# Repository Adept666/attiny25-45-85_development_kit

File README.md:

# attiny25-45-85_development_kit

ATtiny25/45/85 Development Kit

## Author

Igor Ivanov

## License

This project is licensed under GNU General Public License v3.0 or later

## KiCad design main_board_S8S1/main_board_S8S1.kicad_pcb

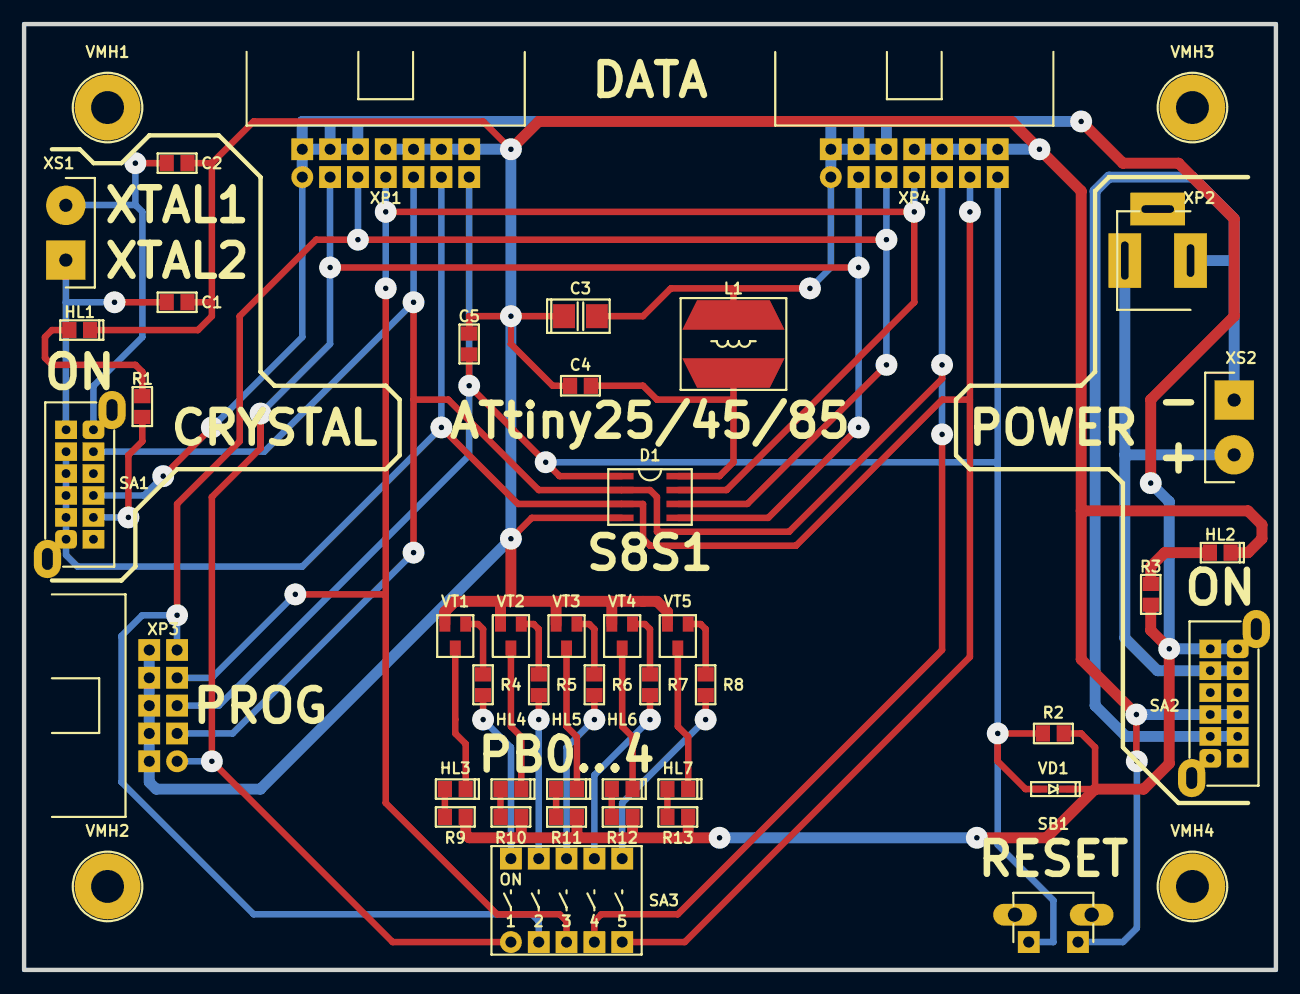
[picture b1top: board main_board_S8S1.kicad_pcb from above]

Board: 2 copper layers, 114.3 x 86.4 mm, 47 parts (0 on the bottom side), 36 nets.

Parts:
C1, C2, C4, C5: CAPACITOR_NON-POLARIZED; C-SMD-0805
C3: CAPACITOR_POLARIZED; CP-SMD-3528
D1: ATtiny25-20SSU; P-SO-08
HL1, HL2, HL3, HL4, HL5, HL6, HL7: DIODE_LIGHT-EMITTING_LEFT; LED-SMD-0805
L1: INDUCTOR_FMC; I-SDR0805
R1, R2, R3, R4, R5, R6, R7, R8, R9, R10, R11, R12, R13: RESISTOR_GENERAL; R-SMD-0805
SA1, SA2: SWITCH_GENERAL_04P_02T; SW-SK-42D01-G
SA3: SWITCH_GENERAL_01P_01T_NO_05U; SW-NDI(R)-05
SB1: SWITCH_BUTTON_NON-LOCK_01P_01T_NO; SW-07125
VD1: DIODE_GENERAL; P-SOD-323
VMH1, VMH2, VMH3, VMH4: VIRTUAL_MOUNTING-HOLE; VMH-STA-DA5
VT1, VT2, VT3, VT4, VT5: BJT_NPN_GENERAL; P-SOT-23
XP1, XP4: CONNECTOR_M_014_20_DATA; CON-IDC-14MR
XP2: CONNECTOR_M_BARREL_SW; CON-PJ-002B
XP3: CONNECTOR_M_010_20_PROG; CON-IDC-10MR
XS1: CONNECTOR_F_002_20_CRYSTAL; CON-DG301R-5.0-02P
XS2: CONNECTOR_F_002_20_POWER; CON-DG301R-5.0-02P

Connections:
/PB0: D1.5, SA3.1COM, XP1.3, XP3.1, XP4.3
/PB1: D1.6, SA3.2COM, XP1.5, XP3.9, XP4.5
/PB2: D1.7, SA3.3COM, XP1.7, XP3.7, XP4.7
/PB3: D1.2, SA1.COM1, SA3.4COM, XP1.9, XP3.3, XP4.9
/PB4: D1.3, SA1.COM3, SA1.COM4, SA1.NC4, SA1.NO3, SA1.NO4, SA3.5COM, XP1.11, XP4.11
/PB5: C5.1, D1.1, R2.2, SB1.NO, VD1.A, XP1.13, XP3.5, XP4.13
/VCC: C4.1, D1.8, L1.2
COM: C1.2, C2.2, C3.-, C4.2, C5.2, D1.4, HL1.C, HL2.C, SA2.NO1, SA2.NO3, SB1.COM, VT1.E, VT2.E, VT3.E, VT4.E, VT5.E, XP1.8, XP1.10, XP1.12, XP1.14, XP3.2, XP3.4, XP3.6, XP3.8, XP3.10, XP4.8, XP4.10, XP4.12, XP4.14
unnamed: C1.1, SA1.NC3, XS1.2
unnamed: C2.1, SA1.NC1, XS1.1
unnamed: HL1.A, R1.2
unnamed: HL2.A, R3.2
unnamed: HL3.A, R9.1
unnamed: HL3.C, VT1.C
unnamed: HL4.A, R10.1
unnamed: HL4.C, VT2.C
unnamed: HL5.A, R11.1
unnamed: HL5.C, VT3.C
unnamed: HL6.A, R12.1
unnamed: HL6.C, VT4.C
unnamed: HL7.A, R13.1
unnamed: HL7.C, VT5.C
unnamed: R1.1, SA1.COM2
unnamed: R4.1, SA3.1NO
unnamed: R4.2, VT1.B
unnamed: R5.1, SA3.2NO
unnamed: R5.2, VT2.B
unnamed: R6.1, SA3.3NO
unnamed: R6.2, VT3.B
unnamed: R7.1, SA3.4NO
unnamed: R7.2, VT4.B
unnamed: R8.1, SA3.5NO
unnamed: R8.2, VT5.B
unnamed: SA2.COM1, SA2.COM3, XS2.2
unnamed: SA2.COM2, SA2.COM4, XS2.1
V: C3.+, L1.1, R2.1, R3.1, R9.2, R10.2, R11.2, R12.2, R13.2, SA1.NC2, SA2.NO2, SA2.NO4, VD1.C, XP1.1, XP1.2, XP1.4, XP1.6, XP4.1, XP4.2, XP4.4, XP4.6

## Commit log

2018-04-19 Add files via upload
    ATtiny debug board
2018-08-10 Rename ATtiny25 debug board. Main board-cache.lib to main_board_S8S1-cache.lib
2018-08-10 Rename main_board_S8S1-cache.lib to main_board_S8S1/main_board_S8S1-cache.lib
2018-08-10 Rename ATtiny25 debug board. Main board.kicad_pcb to main_board_S8S1/main_board_S8S1.kicad_pcb
2018-08-10 Rename ATtiny25 debug board. Main board.net to main_board_S8S1/main_board_S8S1.net
2018-08-10 Rename ATtiny25 debug board. Main board.pro to main_board_S8S1/main_board_S8S1.pro
2018-08-10 Rename ATtiny25 debug board. Main board.sch to main_board_S8S1/main_board_S8S1.sch
2018-08-10 Rename KCPL.lib to main_board_S8S1/KCPL.lib
2018-08-10 Толщина линий на слое Edge.Cuts увеличена до 0,4 мм
2018-08-10 Заменён футпринт контроллера
2018-08-10 Заменён футпринт контроллера, изменены номиналы R1 и R3
2018-08-10 Заменён символ контроллера
2018-08-13 Обновлены футпринты ключей
2018-08-13 Обновлён футпринт диода
2018-08-13 Все слои сделаны видимыми
2018-08-13 Чертежи подписаны
2018-08-17 Обновлены футпринты разъёмов и ключей
2018-08-17 Обновлены футпринты светодиодов
2018-10-29 Удалён файл нетлиста
2018-10-29 Обновлены футпринты светодиодов HL1, HL2
2018-10-29 Доработаны трассы, а также линии на слое F.SilkS (разделённые линии заменены цельными)
2018-10-29 Удалён файл библиотеки main_board_S8S1-cache.lib
2018-10-29 Файл библиотеки символов переименован в соответствии с названием проекта
2018-10-31 В связи с доработкой библиотеки обновлено большинство футпринтов
2019-02-17 Создан файл README.md
2019-02-17 Создано изображение схемы
2019-02-17 В README.md добавлено изображение схемы
2019-02-17 Изменена толщина печатной платы
2019-02-17 Буквенная нумерация составных частей компонентов заменена на цифровую
2019-02-17 Подписаны разъёмы, переключатели, светодиоды и ИМС. Скрыты имена футпринтов. Показана мощность резисторов. Свойства текстовых полей УГО приведены к единообразию
2019-02-17 Свойства текстовых полей составных частей УГО ключа SA3 приведены к единообразию
2019-02-17 Отключены неиспользуемые слои Adhes и Paste
2019-02-17 Отредактирована библиотека проекта. Обновлена схема и плата
2019-02-17 Применены собственные символы общей точки и питания. Завершено обновление схемы после дорабоки бибиотеки проекта
2019-02-18 В связи с доработкой библиотеки обновлены футпринты ключей
2019-02-18 Корректно выбраны значения свойства Placement Type футпринтов
2019-02-18 Обновлены футпринты (удалены примитивы на слое F.Paste)
2019-02-18 Спроектированы варианты основных плат для МК в корпусах 8P3 и 8S2. Повторно выбраны значения свойсва Placement Type футпринтов
2019-05-15 Обновлены УГО ИМС
2019-05-15 Незначительно отредактированы платы
2019-05-15 Основные надписи схем дополнены комментариями о лицензии
2019-05-15 Основные надписи плат дополнены комментариями о лицензии
2019-05-15 Обновлены изображения схем. Увеличена толщина линий
2019-07-12 Символы HOLE заменены на символы VIRTUAL_MOUNTING-HOLE. Скорректировано положение некоторых надписей слоя F.Fab
2019-07-12 Изображены соединения на шинах
2019-09-02 Обновлены футпринты разъёмов IDC
2019-09-02 Скорректированы библиотеки проектов
2019-09-04 Схемы и платы обновлены в связи с переименованием футпринта стойки VMH-STA-DA5
2019-09-04 Схемы скорректированы с учётом изменений в УГО переключателей
2019-09-04 Платы скорректированы с учётом изменений в ФП переключателей
2019-09-06 Незначительно оптимизирована трассировка
2019-09-13 Платы обновлены в связи с изменением футпринта VMH-STA-DA5
2019-11-04 Платы обновлены в связи с изменением футпринта CON-PJ-002B
2019-11-04 Исправлена ошибка в имени символа переключателя SA3
2019-11-04 Платы обновлены в связи с переименованием футпринтов катушек индуктивности
2019-11-04 Корректно выбраны значения свойства Placement Type виртуальных футпринтов
2020-03-05 Созданы файлы sym-lib-table
2020-03-05 Удалено отчество в README.md
2020-03-05 Отредактированы схемы (заменено УГО разъёма питания, удалено отчество в основной надписи)
2020-03-05 Отредактированы чертежи плат (обновлён ФП разъёма питания, удалено отчество в основной надписи)
